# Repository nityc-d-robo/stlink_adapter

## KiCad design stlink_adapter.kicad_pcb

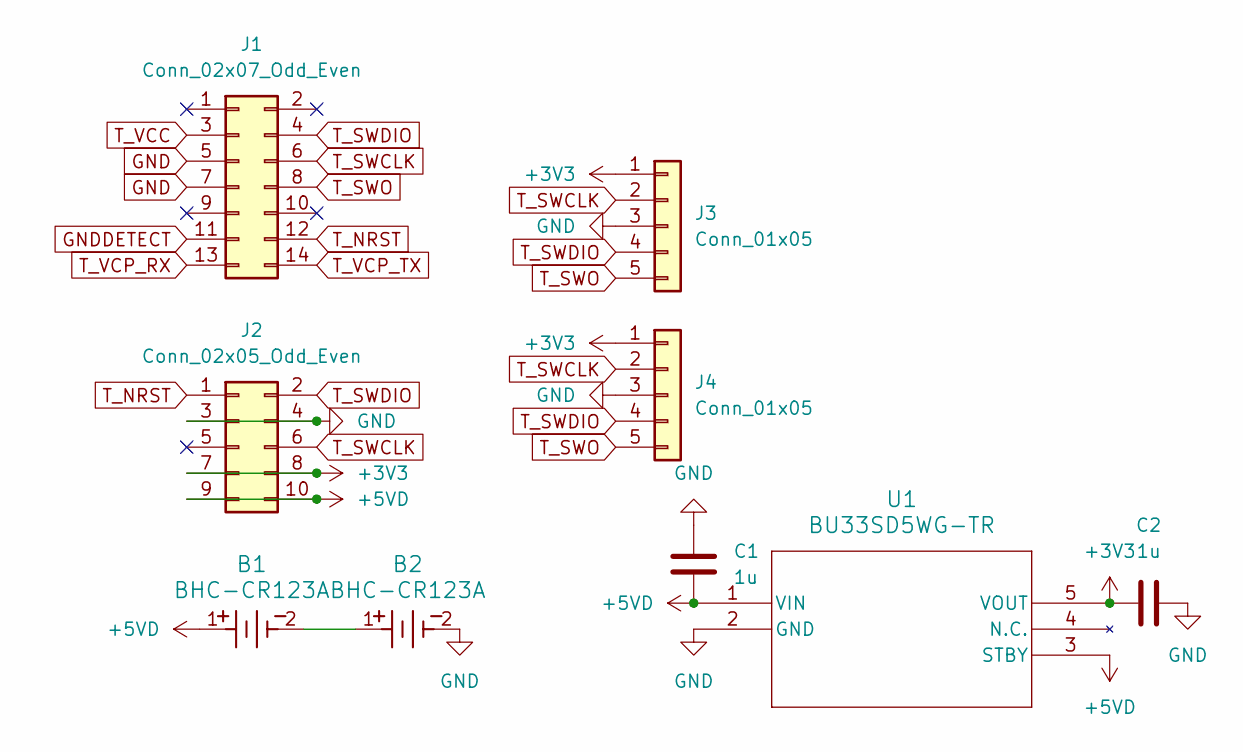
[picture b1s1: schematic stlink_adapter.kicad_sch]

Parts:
B1, B2: BHC-CR123A
C1, C2: 1u; C_0603_1608Metric
J1: Conn_02x07_Odd_Even; CONN14_3220-14_CNC
J2: Conn_02x05_Odd_Even; IDC-Header_2x05_P2.54mm_Vertical
J3: Conn_01x05; JST_XH_B5B-XH-A_1x05_P2.50mm_Vertical
J4: Conn_01x05; JST_PH_B5B-PH-K_1x05_P2.00mm_Vertical
U1: BU33SD5WG-TR; SSOP5_ROM

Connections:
+3V3: C2.1, J2.7, J2.8, J3.1, J4.1, U1.5 (VOUT)
+5VD: B1.1, C1.2, J2.9, J2.10, U1.1 (VIN), U1.3 (STBY)
GND: B2.2, C1.1, C2.2, J1.5, J1.7, J2.3, J2.4, J3.3, J4.3, U1.2 (GND)
GNDDETECT: J1.11
unnamed: B1.2, B2.1
T_NRST: J1.12, J2.1
T_SWCLK: J1.6, J2.6, J3.2, J4.2
T_SWDIO: J1.4, J2.2, J3.4, J4.4
T_SWO: J1.8, J3.5, J4.5
T_VCC: J1.3
T_VCP_RX: J1.13
T_VCP_TX: J1.14

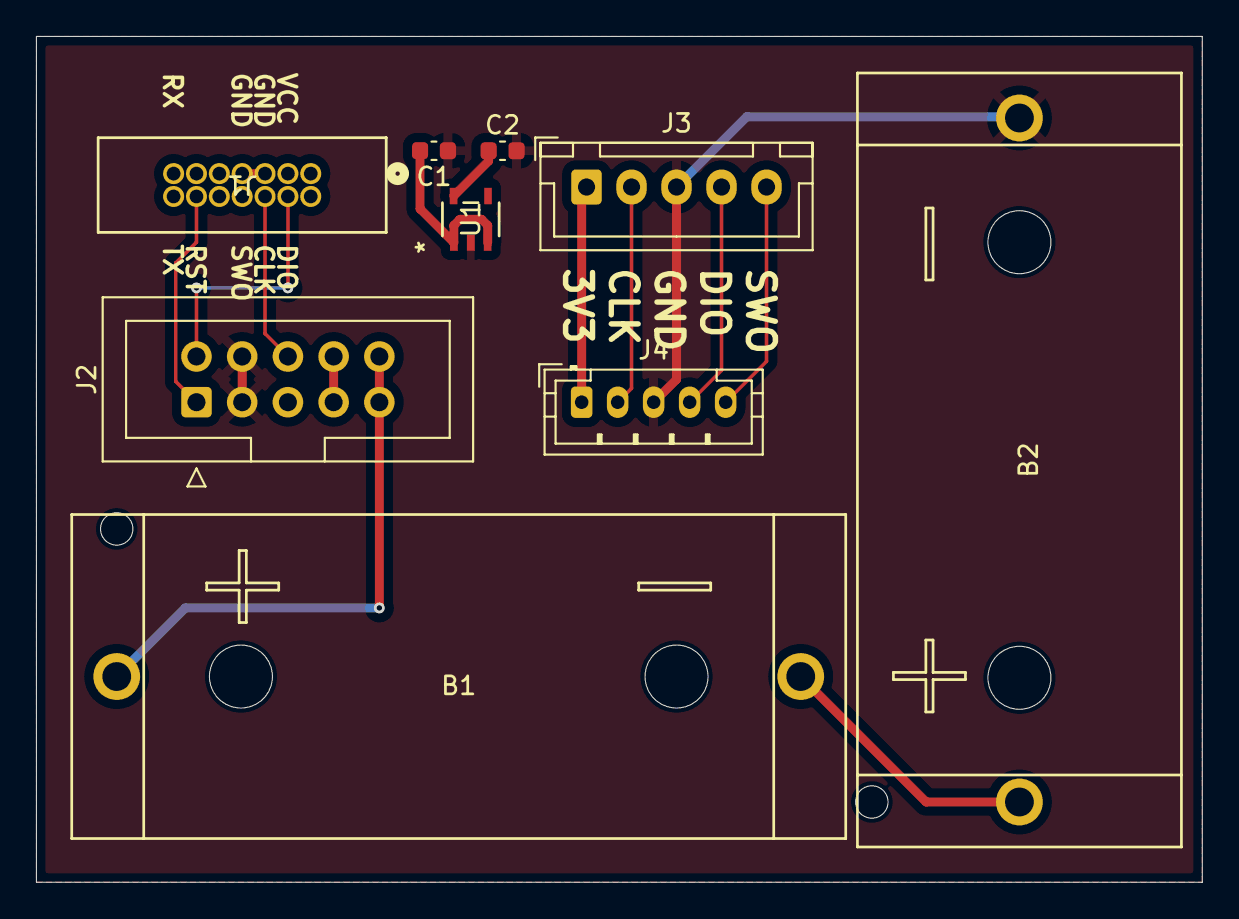
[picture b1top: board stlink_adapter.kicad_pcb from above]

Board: 2 copper layers, 64.8 x 47.0 mm, 9 parts (0 on the bottom side), 8 nets.

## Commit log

2025-04-22 first commit.
